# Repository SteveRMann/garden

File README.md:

# GardenProject
This project is for the solar-powered Wemos D1 mini with a DS18B20 temperature sensor and a Capacitive Moisture sensor.

---------------
Here is a project by Nick Gammon that uses a supercap instead of a battery.
https://www.gammon.com.au/forum/?id=12821

---------------
The publish functions expect char[] types to be passed in rather than Strings.
You need to use the String.toCharArray() function to convert your strings to the necessary type.

char charBuf[50];
stringOne.toCharArray(charBuf, 50)
myString.toCharArray(buf, len)

----------------------
For future reference:
#include <IPAddress.h>
IPAddress ipAddress(192, 168, 0, 1);  

--------

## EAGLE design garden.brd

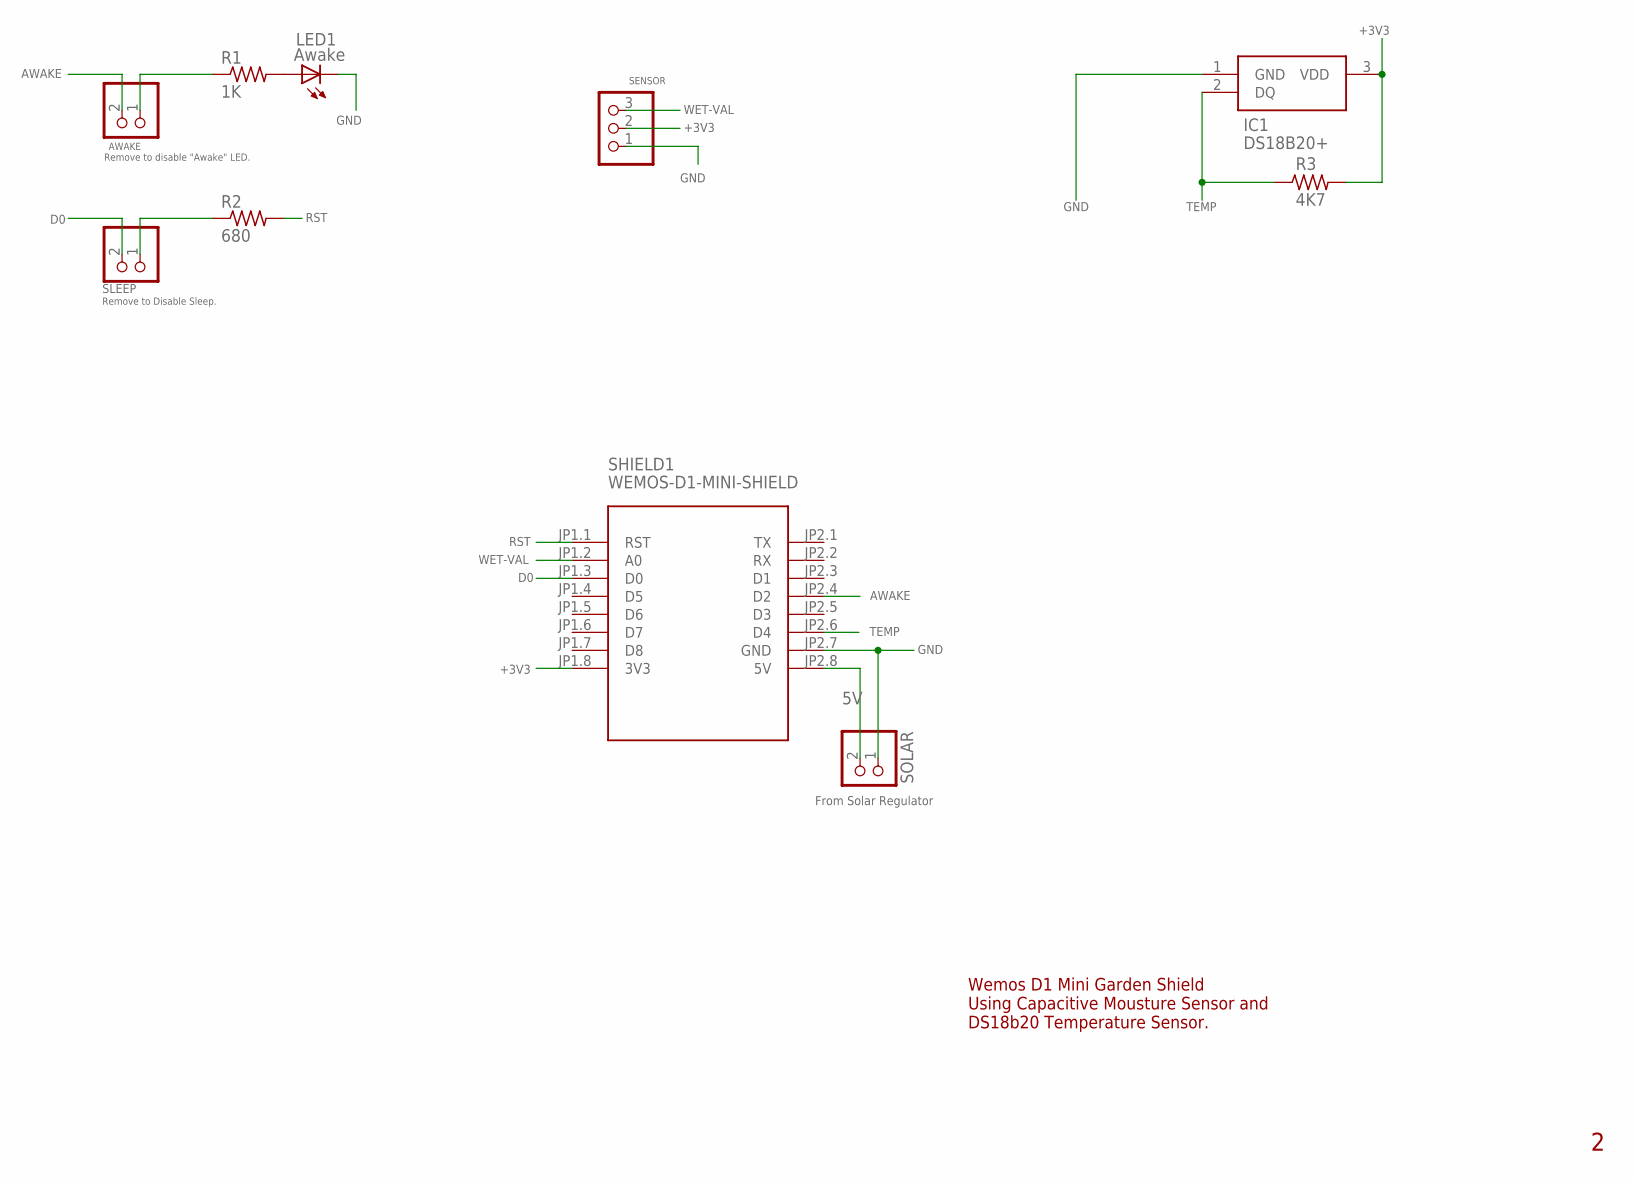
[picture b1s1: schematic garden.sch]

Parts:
AWAKE: Remove to disable "Awake" LED.; 1X02
IC1: DS18B20+; TO-92
LED1: Awake; LED3MM
R1: 1K; 0207/9
R2: 680; 0207/9
R3: 4K7; 0207/9
SENSOR: Moisture Sensor; 1X03/90
SHIELD1: WEMOS-D1-MINI-SHIELD
SLEEP: Remove to Disable Sleep.; 1X02
SOLAR: From Solar Regulator; 1X02/90

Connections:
5V: SHIELD1.JP2.8 (5V), SOLAR.2
+3V3: IC1.3 (VDD), R3.2, SENSOR.2, SHIELD1.JP1.8 (3V3)
AWAKE: AWAKE.2, SHIELD1.JP2.4 (D2)
D0: SHIELD1.JP1.3 (D0), SLEEP.2
GND: IC1.1 (GND), LED1.K (C), SENSOR.1, SHIELD1.JP2.7 (GND), SOLAR.1
unnamed: LED1.A, R1.2
unnamed: AWAKE.1, R1.1
unnamed: R2.1, SLEEP.1
RST: R2.2, SHIELD1.JP1.1 (RST)
TEMP: IC1.2 (DQ), R3.1, SHIELD1.JP2.6 (D4)
WET-VAL: SENSOR.3, SHIELD1.JP1.2 (A0)

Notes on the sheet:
Wemos D1 Mini Garden Shield Using Capacitive Mousture Sensor and DS18b20 Temperature Sensor.

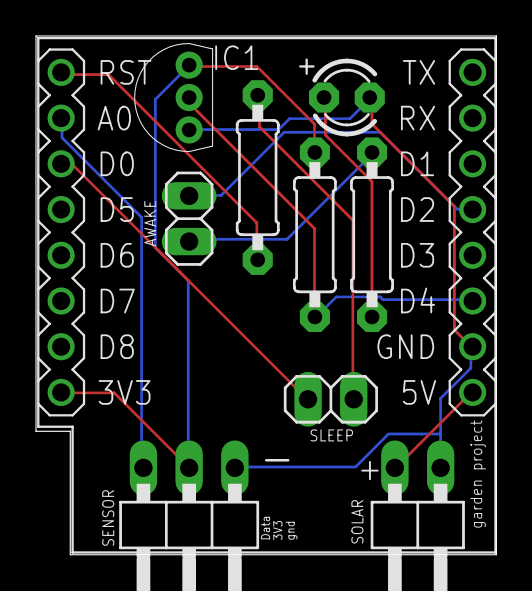
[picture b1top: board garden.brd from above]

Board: 2 copper layers, 25.6 x 28.8 mm, 10 parts (0 on the bottom side), 11 nets.

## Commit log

2020-05-23 Forked from GardenProject.ino
2020-05-25 Add files via upload
    Added Arduino.h to publish data as a JSON string.
2020-05-25 Add files via upload
    -- Version 2.0 --
    5/25/20 - Added separate topics for each publish item. Home Assistant doesn't handle JSON strings well.
2020-10-27 Added schematic of the Moisture Probe
2021-05-04 Changed time between readings
2021-08-16 Added .brd file
2022-04-24 Added micro USB

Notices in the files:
parts and their libraries:
diy-modules: Released under the Creative Commons Attribution 4.0 International License: http://creativecommons.org/licenses/by/4.0
